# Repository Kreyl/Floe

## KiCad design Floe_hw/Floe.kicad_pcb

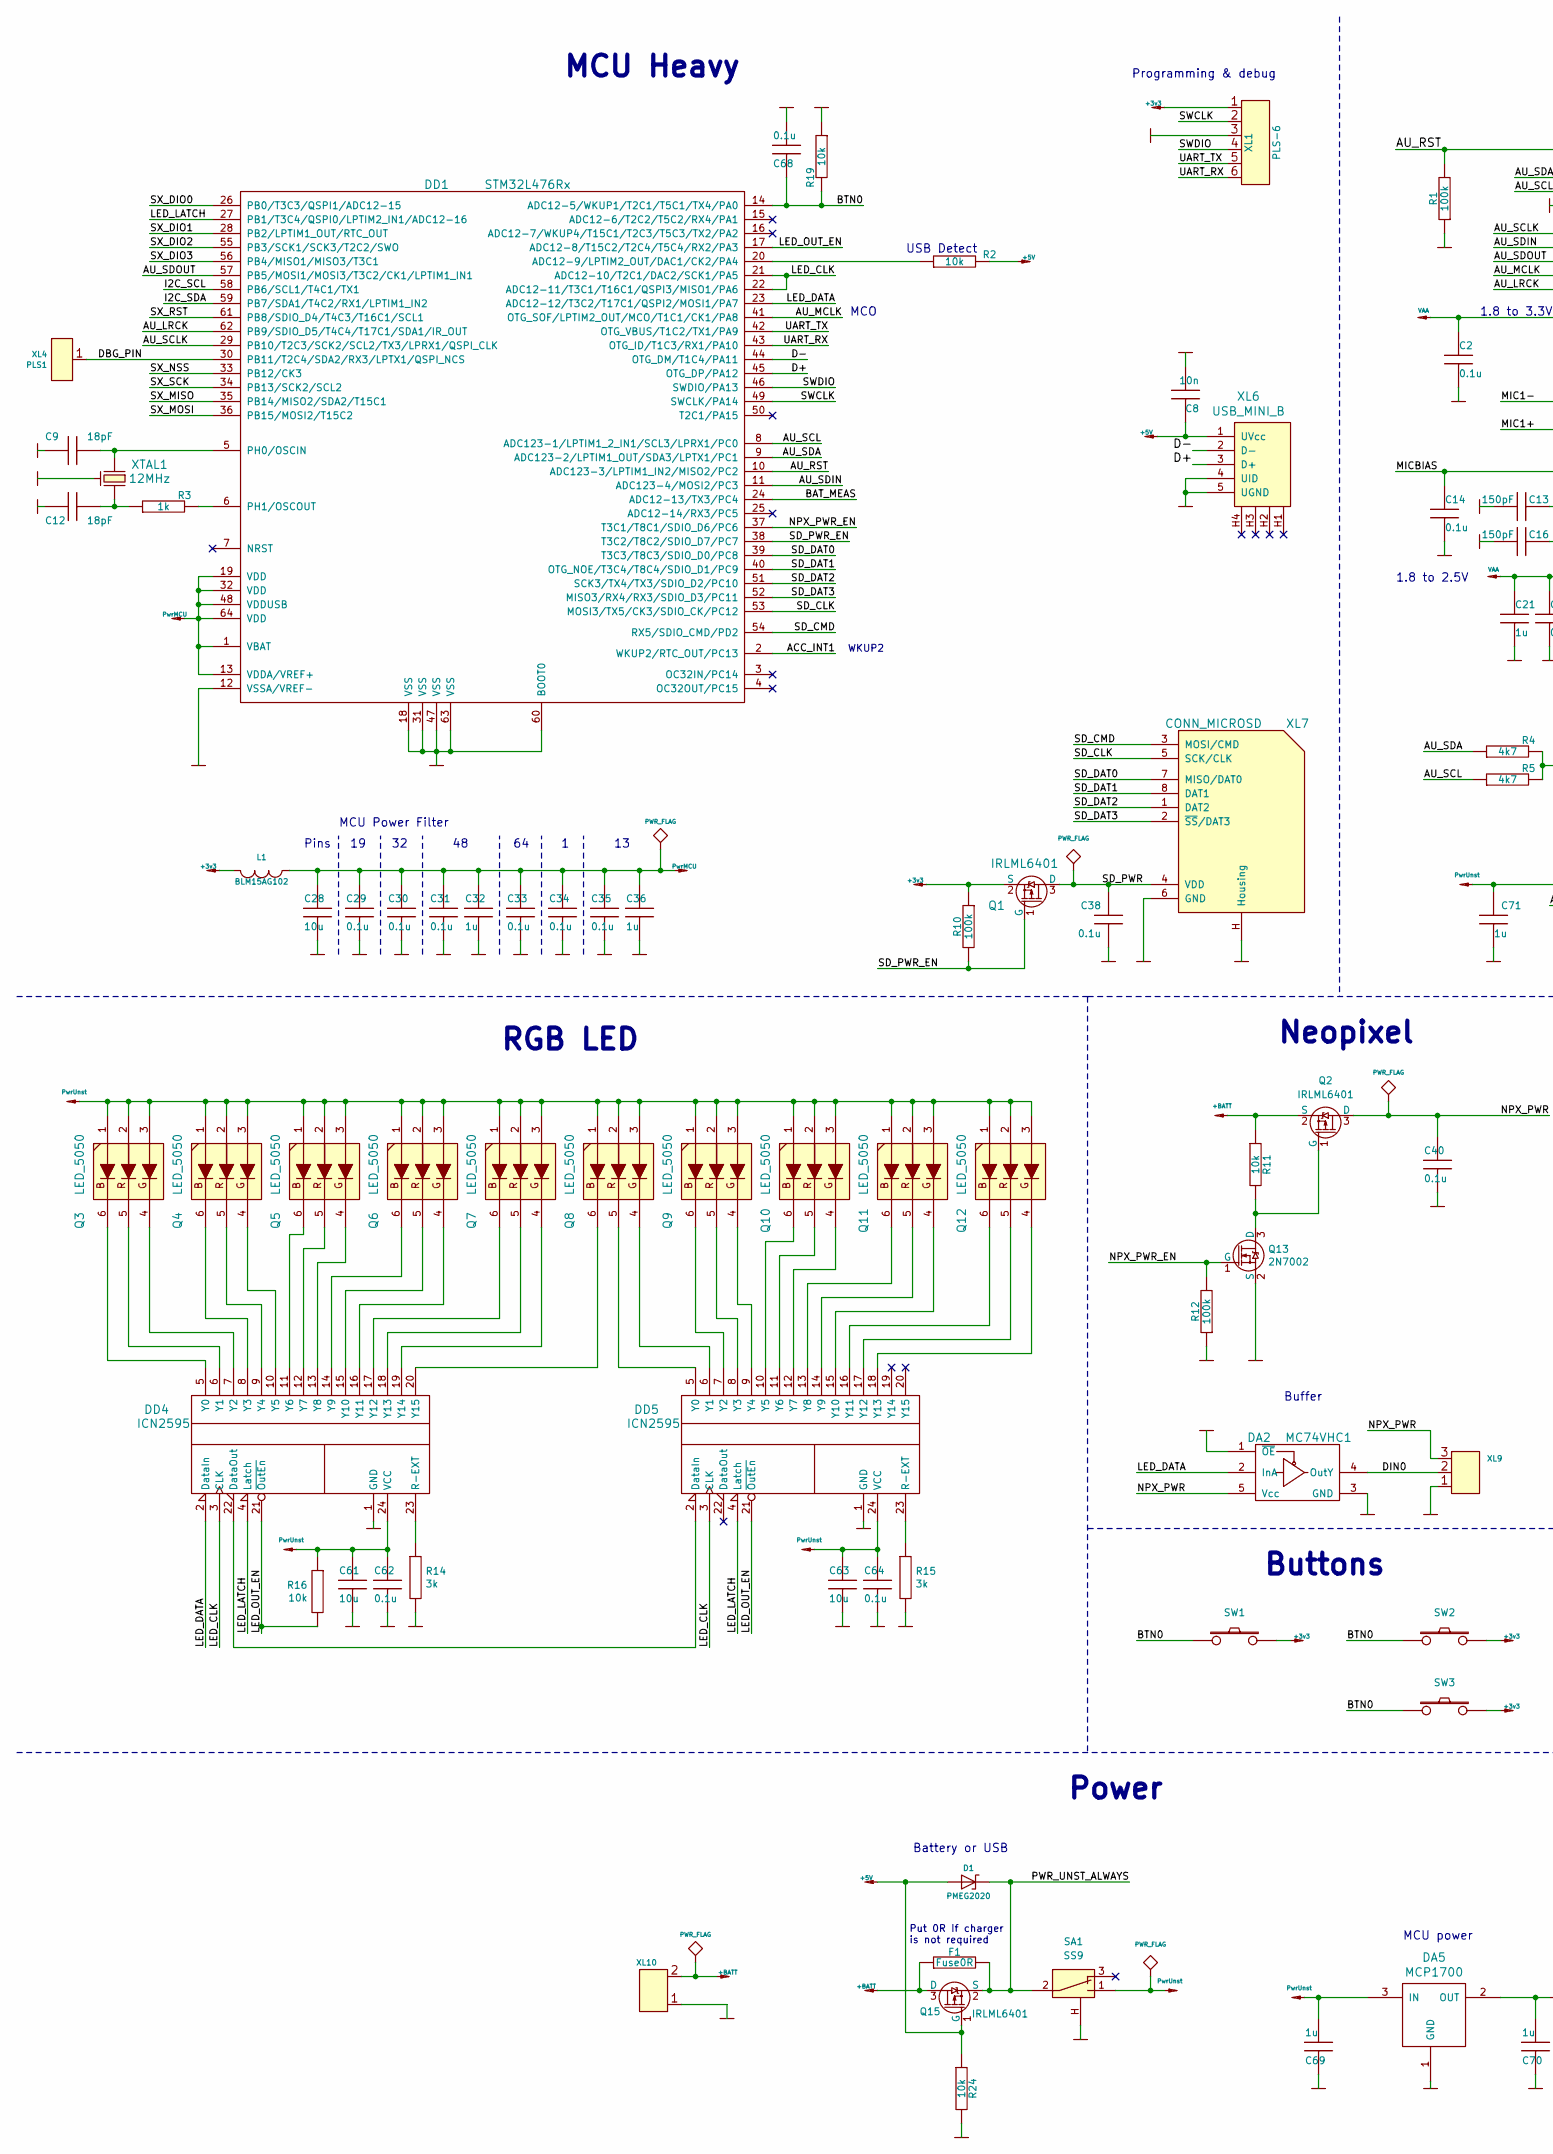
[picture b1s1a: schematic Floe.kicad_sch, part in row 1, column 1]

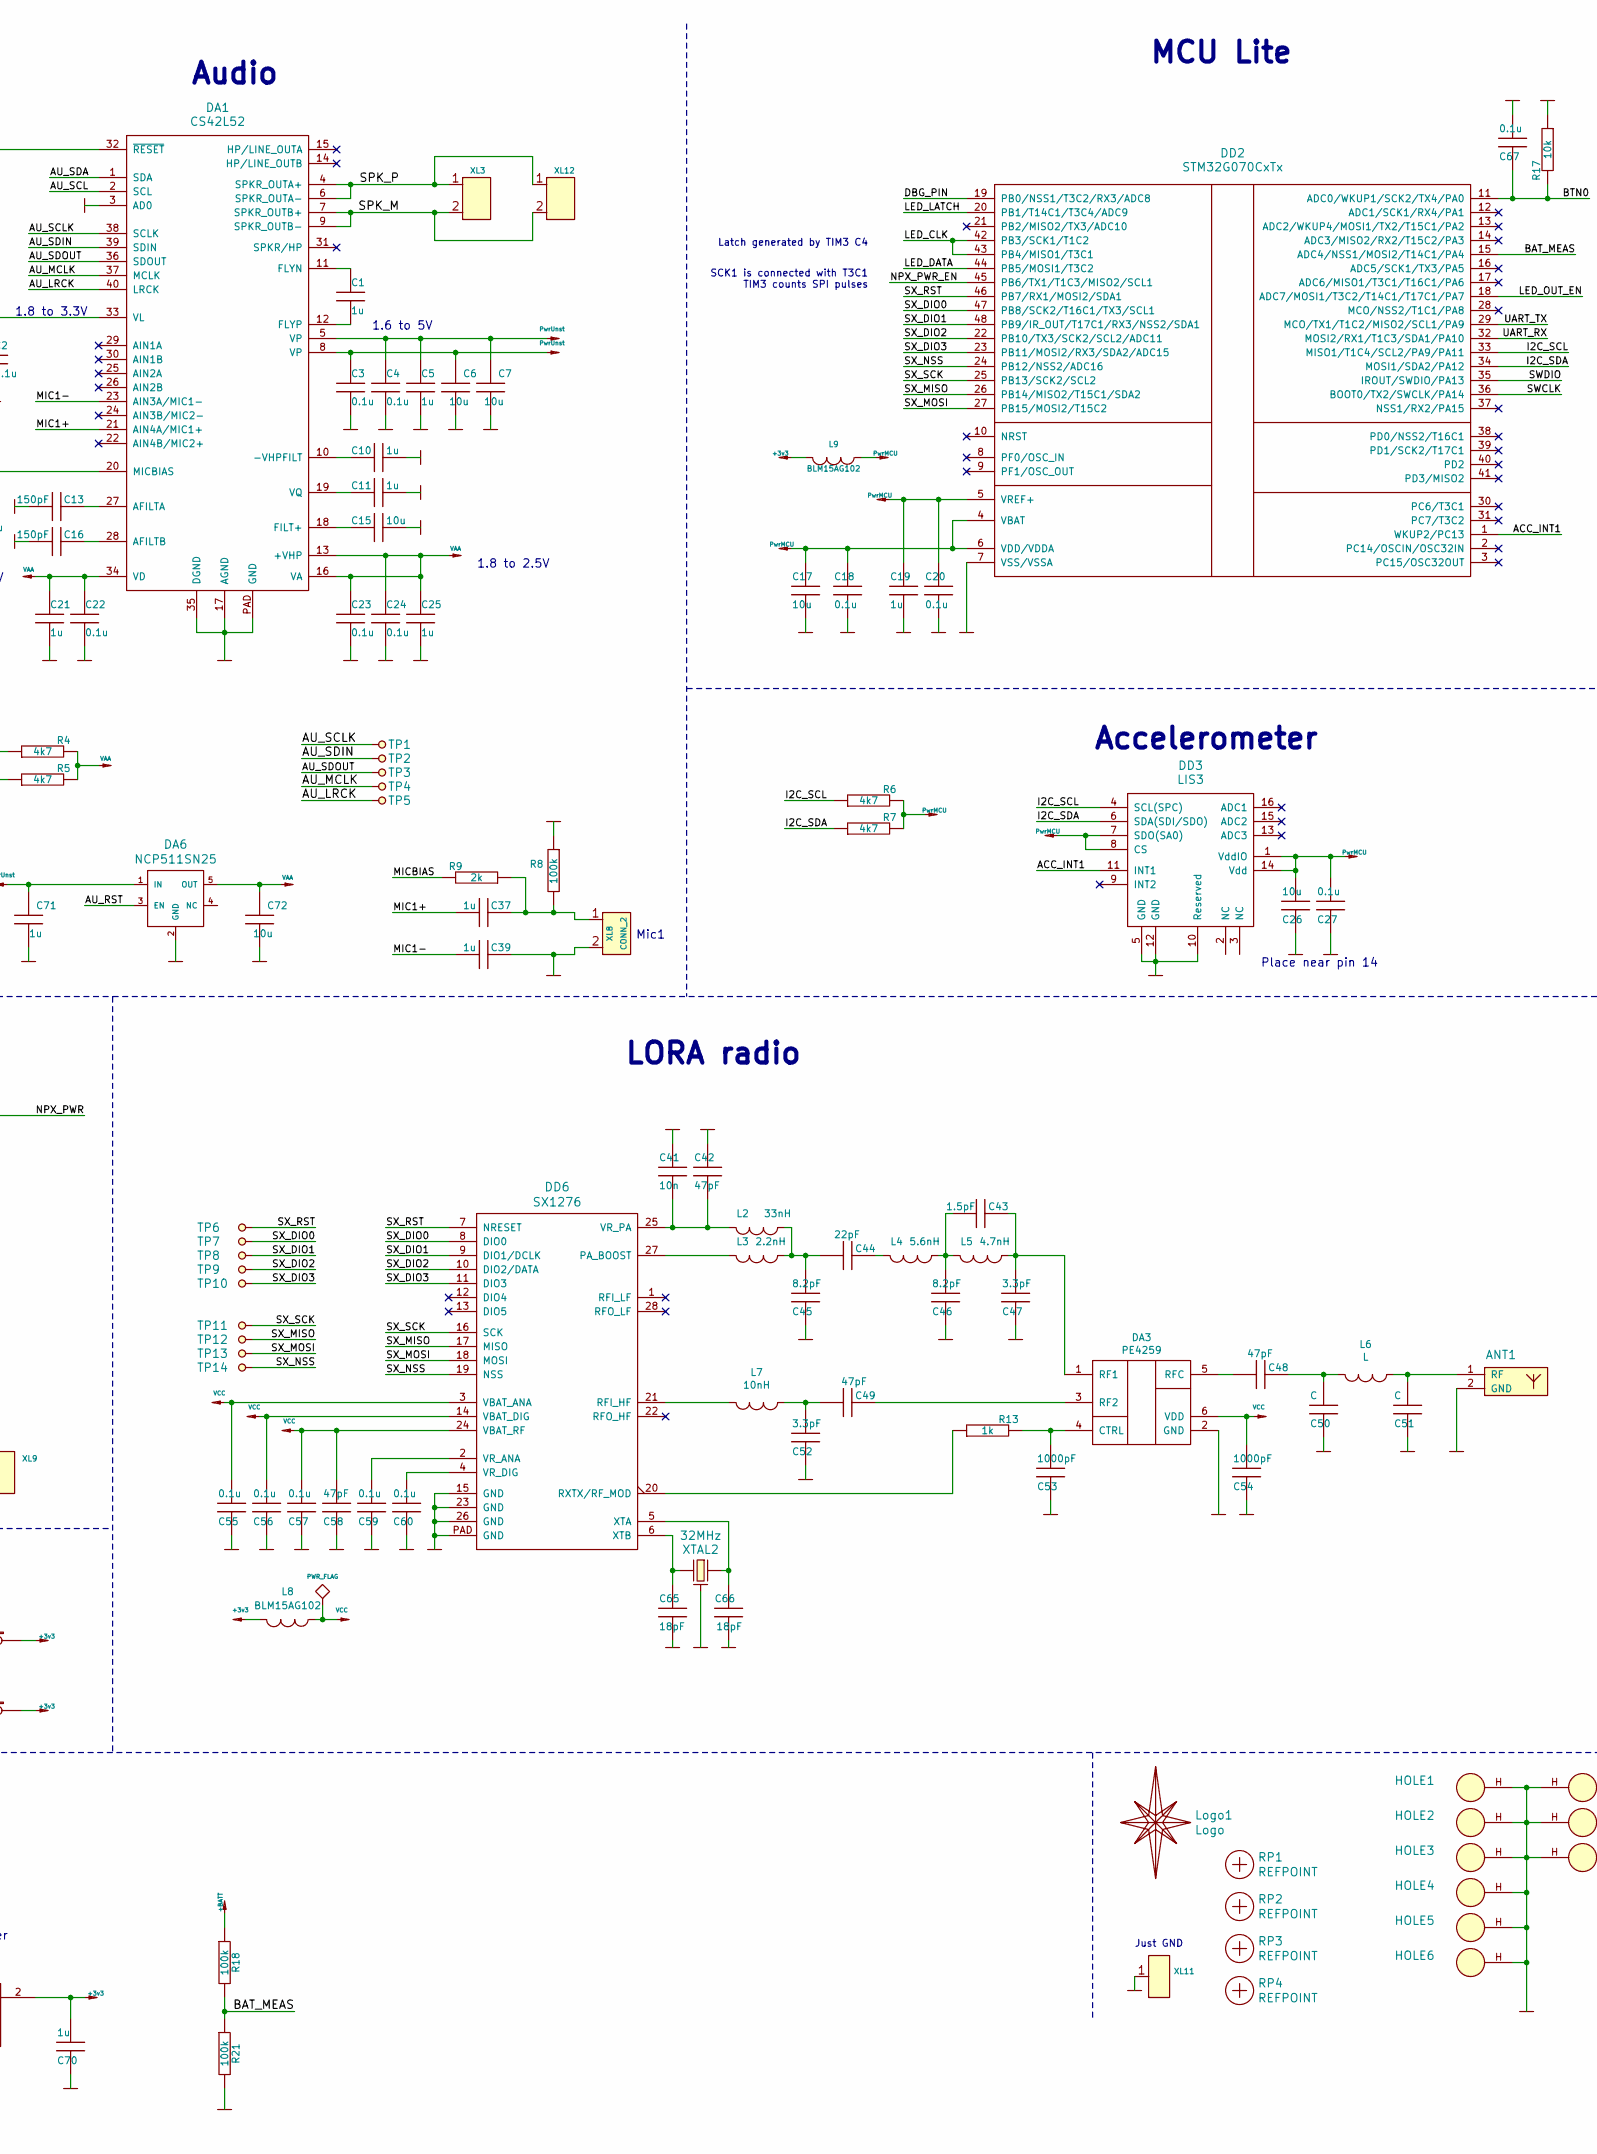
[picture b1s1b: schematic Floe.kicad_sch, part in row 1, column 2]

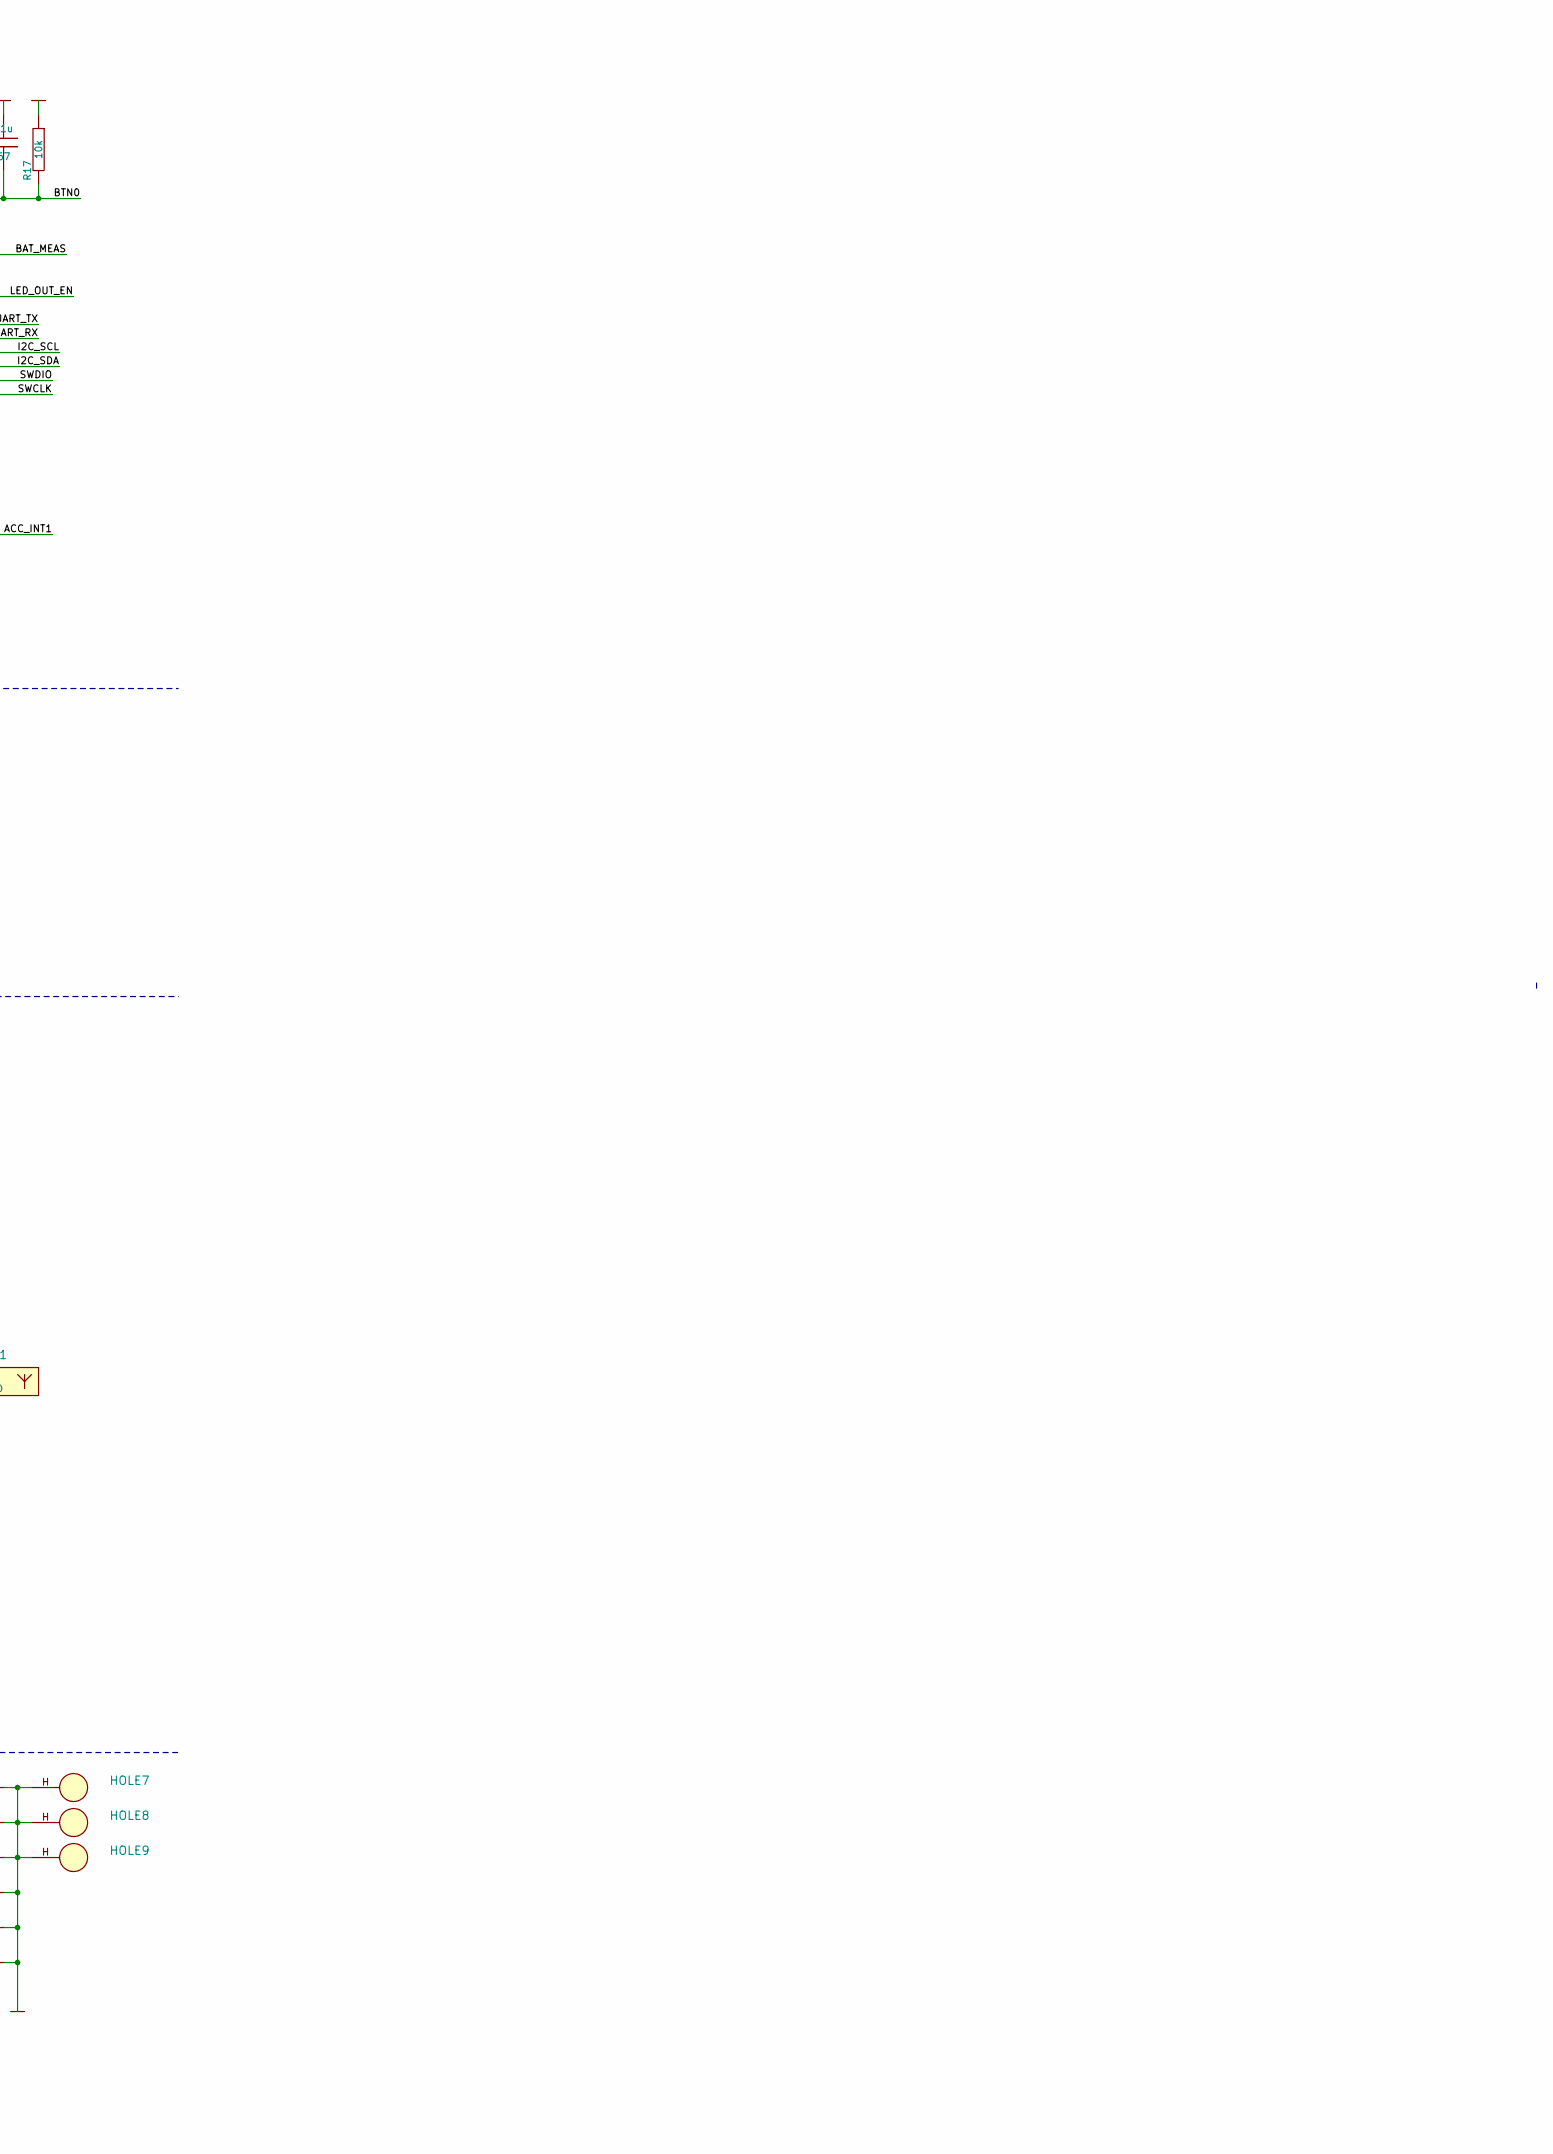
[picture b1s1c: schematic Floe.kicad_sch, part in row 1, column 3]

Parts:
ANT1: ANT_GENERAL; ANT_IFA_MUSHROOM
C1, C5, C10, C11, C19, C21, C25, C32, C36, C37, C39, C69, C70, C71: 1u; CAP_0603_Silks
C2, C3, C4, C14, C18, C20, C22, C23, C24, C27, C29, C30, C31, C33, C34, C35, C38, C40, C62, C64, C67, C68: 0.1u; CAP_0603_Silks
C6, C7, C15, C17, C26, C28, C61, C63, C72: 10u; CAP_0603_Silks
C8: 10n; CAP_0603_Silks
C9, C12, C65, C66: 18pF; CAP_0603_Silks
C13, C16: 150pF; CAP_0603_Silks
C41: 10n; CAP_0402
C42, C48, C49, C58: 47pF; CAP_0402
C43: 1.5pF; CAP_0402
C44: 22pF; CAP_0402
C45, C46: 8.2pF; CAP_0402
C47, C52: 3.3pF; CAP_0402
C50, C51: C; CAP_0402
C53, C54: 1000pF; CAP_0402
C55, C56, C57, C59, C60: 0.1u; CAP_0402
D1: PMEG2020; SOD323
DA1: CS42L52; QFN40
DA2: MC74VHC1; SOT23-5
DA3: PE4259; SC70
DA5: MCP1700; SOT23-3A
DA6: NCP511SN25; SOT23-5
DD1: STM32L476Rx; LQFP64
DD2: STM32G070CxTx; LQFP48
DD3: LIS3; LGA16_3X3_5_3
DD4, DD5: ICN2595; TSSOP24_150_0635
DD6: SX1276; QFN-28_EP_6x6_Pitch0.65mm
F1: Fuse0R; RES_0603_FUSE
HOLE1, HOLE2, HOLE3, HOLE4, HOLE5, HOLE6: HOLE_METALLED; Hole3d5_out10mm
HOLE7, HOLE8, HOLE9: HOLE_METALLED; Hole3d3_out5d5mm
L1, L8, L9: BLM15AG102; IND_0402
L2: 33nH; IND_0402
L3: 2.2nH; IND_0402
L4: 5.6nH; IND_0402
L5: 4.7nH; IND_0402
L6: L; IND_0402
L7: 10nH; IND_0402
Logo1: Logo; Ostranna_16d9_13d5
Q1, Q2, Q15: IRLML6401; SOT23-3
Q3, Q4, Q5, Q6, Q7, Q8, Q9, Q10, Q11, Q12: LED_5050
Q13: 2N7002; SOT23-3
R1, R8, R10, R12, R18, R21: 100k; RES_0603
R2, R11, R16, R17, R19, R24: 10k; RES_0603
R3, R13: 1k; RES_0603
R4, R5, R6, R7: 4k7; RES_0603
R9: 2k; RES_0603
R14, R15: 3k; RES_0603
RP1, RP2, RP3, RP4: REFPOINT; REF_POINT_2MM
SA1: SS9; SW_SS9
SW1, SW2, SW3: BUTTON; BTN_4x4_SMD
TP1, TP2, TP3, TP4, TP5, TP6, TP7, TP8, TP9, TP10, TP11, TP12, TP13, TP14: TESTPOINT; TESTPOINT_1MM
XL1: PLS-6; PLS-6_LOCK
XL3: CONN_2; WB-02(MW-2M)
XL4: PLS1; PLS-1Rnd
XL6: USB_MINI_B; USBmicro_MOLEX_1050170001
XL7: CONN_MICROSD; MICROSD_CAP_FIX05A
XL8: CONN_2; WB-02(MW-2M)LongContacts
XL9: CONN_3; SLD_3_2D5
XL10, XL12: CONN_2; SLD_2_2D5_1mm
XL11: CONN_1; PLS-1Rnd
XTAL1: 12MHz; 03225C4
XTAL2: 32MHz; 03225C4

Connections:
+3v3: C70.1, DA5.2 (OUT), L1.2, L8.2, L9.2, Q1.2 (S), R10.1, SW1.2, SW2.2, SW3.2, XL1.1
+5v: C8.2, D1.A, Q15.1 (G), R2.2, R24.1, XL6.1 (UVcc)
+BATT: F1.1, Q2.2 (S), Q15.3 (D), R11.1, R18.1, XL10.2 (PM)
/ACC_INT1: DD1.2 (WKUP2/RTC_OUT/PC13), DD2.1 (WKUP2/PC13), DD3.11 (INT1)
/AU_LRCK: DA1.40 (LRCK), DD1.62 (PB9/SDIO_D5/T4C4/T17C1/SDA1/IR_OUT), TP5.1
/AU_MCLK: DA1.37 (MCLK), DD1.41 (OTG_SOF/LPTIM2_OUT/MCO/T1C1/CK1/PA8), TP4.1
/AU_RST: DA1.32 (~RESET), DA6.3 (EN), DD1.10 (ADC123-3/LPTIM1_IN2/MISO2/PC2), R1.2
/AU_SCL: DA1.2 (SCL), DD1.8 (ADC123-1/LPTIM1_2_IN1/SCL3/LPRX1/PC0), R5.1
/AU_SCLK: DA1.38 (SCLK), DD1.29 (PB10/T2C3/SCK2/SCL2/TX3/LPRX1/QSPI_CLK), TP1.1
/AU_SDA: DA1.1 (SDA), DD1.9 (ADC123-2/LPTIM1_OUT/SDA3/LPTX1/PC1), R4.1
/AU_SDIN: DA1.39 (SDIN), DD1.11 (ADC123-4/MOSI2/PC3), TP2.1
/AU_SDOUT: DA1.36 (SDOUT), DD1.57 (PB5/MOSI1/MOSI3/T3C2/CK1/LPTIM1_IN1), TP3.1
/BAT_MEAS: DD1.24 (ADC12-13/TX3/PC4), DD2.15 (ADC4/NSS1/MOSI2/T14C1/PA4), R18.2, R21.1
/BTN0: C67.2, C68.2, DD1.14 (ADC12-5/WKUP1/T2C1/T5C1/TX4/PA0), DD2.11 (ADC0/WKUP1/SCK2/TX4/PA0), R17.2, R19.2, SW1.1, SW2.1, SW3.1
/D+: DD1.45 (OTG_DP/PA12), XL6.3 (D+)
/D-: DD1.44 (OTG_DM/T1C4/PA11), XL6.2 (D-)
/DBG_PIN: DD1.30 (PB11/T2C4/SDA2/RX3/LPTX1/QSPI_NCS), DD2.19 (PB0/NSS1/T3C2/RX3/ADC8), XL4.1
/DIN0: DA2.4 (OutY), XL9.2 (PM)
/I2C_SCL: DD1.58 (PB6/SCL1/T4C1/TX1), DD2.33 (MISO1/T1C4/SCL2/PA9/PA11), DD3.4 (SCL(SPC)), R6.1
/I2C_SDA: DD1.59 (PB7/SDA1/T4C2/RX1/LPTIM1_IN2), DD2.34 (MOSI1/SDA2/PA12), DD3.6 (SDA(SDI/SDO)), R7.1
/LED_CLK: DD1.21 (ADC12-10/T2C1/DAC2/SCK1/PA5), DD1.22 (ADC12-11/T3C1/T16C1/QSPI3/MISO1/PA6), DD2.42 (PB3/SCK1/T1C2), DD2.43 (PB4/MISO1/T3C1), DD4.3 (CLK), DD5.3 (CLK)
/LED_DATA: DA2.2 (InA), DD1.23 (ADC12-12/T3C2/T17C1/QSPI2/MOSI1/PA7), DD2.44 (PB5/MOSI1/T3C2), DD4.2 (DataIn)
/LED_LATCH: DD1.27 (PB1/T3C4/QSPI0/LPTIM2_IN1/ADC12-16), DD2.20 (PB1/T14C1/T3C4/ADC9), DD4.4 (Latch), DD5.4 (Latch)
/LED_OUT_EN: DD1.17 (ADC12-8/T15C2/T2C4/T5C4/RX2/PA3), DD2.18 (ADC7/MOSI1/T3C2/T14C1/T17C1/PA7), DD4.21 (~OutEn), DD5.21 (~OutEn), R16.2
/MIC1+: C37.1, DA1.21 (AIN4A/MIC1+)
/MIC1-: C39.1, DA1.23 (AIN3A/MIC1-)
/MICBIAS: C14.1, DA1.20 (MICBIAS), R9.2
/NPX_PWR: C40.2, DA2.5 (Vcc), Q2.3 (D), XL9.3
/NPX_PWR_EN: DD1.37 (T3C1/T8C1/SDIO_D6/PC6), DD2.45 (PB6/TX1/T1C3/MISO2/SCL1), Q13.1 (G), R12.2
/PWR_UNST_ALWAYS: D1.C, F1.2, Q15.2 (S), SA1.2
/SD_CLK: DD1.53 (MOSI3/TX5/CK3/SDIO_CK/PC12), XL7.5 (SCK/CLK)
/SD_CMD: DD1.54 (RX5/SDIO_CMD/PD2), XL7.3 (MOSI/CMD)
/SD_DAT0: DD1.39 (T3C3/T8C3/SDIO_D0/PC8), XL7.7 (MISO/DAT0)
/SD_DAT1: DD1.40 (OTG_NOE/T3C4/T8C4/SDIO_D1/PC9), XL7.8 (DAT1)
/SD_DAT2: DD1.51 (SCK3/TX4/TX3/SDIO_D2/PC10), XL7.1 (DAT2)
/SD_DAT3: DD1.52 (MISO3/RX4/RX3/SDIO_D3/PC11), XL7.2 (~SS~/DAT3)
/SD_PWR: C38.1, Q1.3 (D), XL7.4 (VDD)
/SD_PWR_EN: DD1.38 (T3C2/T8C2/SDIO_D7/PC7), Q1.1 (G), R10.2
/SPK_M: DA1.7 (SPKR_OUTB+), DA1.9 (SPKR_OUTB-), XL3.2 (PM), XL12.2 (PM)
/SPK_P: DA1.4 (SPKR_OUTA+), DA1.6 (SPKR_OUTA-), XL3.1, XL12.1
/SWCLK: DD1.49 (SWCLK/PA14), DD2.36 (BOOT0/TX2/SWCLK/PA14), XL1.2
/SWDIO: DD1.46 (SWDIO/PA13), DD2.35 (IROUT/SWDIO/PA13), XL1.4
/SX_DIO0: DD1.26 (PB0/T3C3/QSPI1/ADC12-15), DD2.47 (PB8/SCK2/T16C1/TX3/SCL1), DD6.8 (DIO0), TP7.1
/SX_DIO1: DD1.28 (PB2/LPTIM1_OUT/RTC_OUT), DD2.48 (PB9/IR_OUT/T17C1/RX3/NSS2/SDA1), DD6.9 (DIO1/DCLK), TP8.1
/SX_DIO2: DD1.55 (PB3/SCK1/SCK3/T2C2/SWO), DD2.22 (PB10/TX3/SCK2/SCL2/ADC11), DD6.10 (DIO2/DATA), TP9.1
/SX_DIO3: DD1.56 (PB4/MISO1/MISO3/T3C1), DD2.23 (PB11/MOSI2/RX3/SDA2/ADC15), DD6.11 (DIO3), TP10.1
/SX_MISO: DD1.35 (PB14/MISO2/SDA2/T15C1), DD2.26 (PB14/MISO2/T15C1/SDA2), DD6.17 (MISO), TP12.1
/SX_MOSI: DD1.36 (PB15/MOSI2/T15C2), DD2.27 (PB15/MOSI2/T15C2), DD6.18 (MOSI), TP13.1
/SX_NSS: DD1.33 (PB12/CK3), DD2.24 (PB12/NSS2/ADC16), DD6.19 (NSS), TP14.1
/SX_RST: DD1.61 (PB8/SDIO_D4/T4C3/T16C1/SCL1), DD2.46 (PB7/RX1/MOSI2/SDA1), DD6.7 (NRESET), TP6.1
/SX_SCK: DD1.34 (PB13/SCK2/SCL2), DD2.25 (PB13/SCK2/SCL2), DD6.16 (SCK), TP11.1
/UART_RX: DD1.43 (OTG_ID/T1C3/RX1/PA10), DD2.32 (MOSI2/RX1/T1C3/SDA1/PA10), XL1.6
/UART_TX: DD1.42 (OTG_VBUS/T1C2/TX1/PA9), DD2.29 (MCO/TX1/T1C2/MISO2/SCL1/PA9), XL1.5
GND: ANT1.2 (GND), C2.2, C3.2, C4.2, C5.2, C6.2, C7.2, C8.1, C9.2, C10.1, C11.1, C12.2, C13.1, C14.2, C15.1, C16.1, C17.1, C18.1, C19.1, C20.1, C21.2, C22.2, C23.2, C24.2, C25.2, C26.2, C27.2, C28.1, C29.1, C30.1, C31.1, C32.1, C33.1, C34.1, C35.1, C36.1, C38.2, C39.2, C40.1, C41.2, C42.2, C45.2, C46.2, C47.2, C50.2, C51.2, C52.2, C53.2, C54.2, C55.2, C56.2, C57.2, C58.2, C59.2, C60.2, C61.1, C62.1, C63.1, C64.1, C65.2, C66.2, C67.1, C68.1, C69.2, C70.2, C71.2, C72.2, DA1.3 (AD0), DA1.17 (AGND), DA1.35 (DGND), DA1.PAD (GND), DA2.1 (~OE), DA2.3 (GND), DA3.2 (GND), DA5.1 (GND), DA6.2 (GND), DD1.12 (VSSA/VREF-), DD1.18 (VSS), DD1.31 (VSS), DD1.47 (VSS)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
unnamed: ANT1.1 (RF), C51.1, L6.2
unnamed: C1.1, DA1.11 (FLYN)
unnamed: C1.2, DA1.12 (FLYP)
unnamed: C9.1, DD1.5 (PH0/OSCIN), XTAL1.1
unnamed: C10.2, DA1.10 (-VHPFILT)
unnamed: C11.2, DA1.19 (VQ)
unnamed: C12.1, R3.1, XTAL1.2
unnamed: C13.2, DA1.27 (AFILTA)
unnamed: C15.2, DA1.18 (FILT+)
unnamed: C16.2, DA1.28 (AFILTB)
unnamed: C37.2, R8.2, R9.1, XL8.1
unnamed: C41.1, C42.1, DD6.25 (VR_PA), L2.1
unnamed: C43.1, C47.1, DA3.1 (RF1), L5.2
unnamed: C43.2, C46.1, L4.2, L5.1
unnamed: C44.1, L4.1
unnamed: C44.2, C45.1, L2.2, L3.2
unnamed: C48.1, C50.1, L6.1
unnamed: C48.2, DA3.5 (RFC)
unnamed: C49.1, DA3.3 (RF2)
unnamed: C49.2, C52.1, L7.2
unnamed: C53.1, DA3.4 (CTRL), R13.2
unnamed: C59.1, DD6.2 (VR_ANA)
unnamed: C60.1, DD6.4 (VR_DIG)
unnamed: C65.1, DD6.6 (XTB), XTAL2.2
unnamed: C66.1, DD6.5 (XTA), XTAL2.1
unnamed: DD1.6 (PH1/OSCOUT), R3.2
unnamed: DD1.20 (ADC12-9/LPTIM2_OUT/DAC1/CK2/PA4), R2.1
unnamed: DD4.5 (Y0), Q3.6
unnamed: DD4.6 (Y1), Q3.5 (G)
unnamed: DD4.7 (Y2), Q3.4 (B)
unnamed: DD4.8 (Y3), Q4.6
unnamed: DD4.9 (Y4), Q4.5 (G)
unnamed: DD4.10 (Y5), Q4.4 (B)
unnamed: DD4.11 (Y6), Q5.6
unnamed: DD4.12 (Y7), Q5.5 (G)
unnamed: DD4.13 (Y8), Q5.4 (B)
unnamed: DD4.14 (Y9), Q6.6
unnamed: DD4.15 (Y10), Q6.5 (G)
unnamed: DD4.16 (Y11), Q6.4 (B)
unnamed: DD4.17 (Y12), Q7.6
unnamed: DD4.18 (Y13), Q7.5 (G)
unnamed: DD4.19 (Y14), Q7.4 (B)
unnamed: DD4.20 (Y15), Q8.6
unnamed: DD4.22 (DataOut), DD5.2 (DataIn)
unnamed: DD4.23 (R-EXT), R14.1
unnamed: DD5.5 (Y0), Q8.5 (G)
unnamed: DD5.6 (Y1), Q8.4 (B)
unnamed: DD5.7 (Y2), Q9.6
unnamed: DD5.8 (Y3), Q9.5 (G)
unnamed: DD5.9 (Y4), Q9.4 (B)
unnamed: DD5.10 (Y5), Q10.6
unnamed: DD5.11 (Y6), Q10.5 (G)
unnamed: DD5.12 (Y7), Q10.4 (B)
unnamed: DD5.13 (Y8), Q11.6
unnamed: DD5.14 (Y9), Q11.5 (G)
unnamed: DD5.15 (Y10), Q11.4 (B)
unnamed: DD5.16 (Y11), Q12.6
unnamed: DD5.17 (Y12), Q12.5 (G)
unnamed: DD5.18 (Y13), Q12.4 (B)
unnamed: DD5.23 (R-EXT), R15.1
unnamed: DD6.20 (RXTX/RF_MOD), R13.1
unnamed: DD6.21 (RFI_HF), L7.1
unnamed: DD6.27 (PA_BOOST), L3.1
unnamed: Q2.1 (G), Q13.3 (D), R11.2
PwrMCU: C17.2, C18.2, C19.2, C20.2, C26.1, C27.1, C28.2, C29.2, C30.2, C31.2, C32.2, C33.2, C34.2, C35.2, C36.2, DD1.1 (VBAT), DD1.13 (VDDA/VREF+), DD1.19 (VDD), DD1.32 (VDD), DD1.48 (VDDUSB), DD1.64 (VDD), DD2.4 (VBAT), DD2.5 (VREF+), DD2.6 (VDD/VDDA), DD3.1 (VddIO), DD3.7 (SDO(SA0)), DD3.8 (CS), DD3.14 (Vdd), L1.1, L9.1, R6.2, R7.2
PwrUnst: C3.1, C4.1, C5.1, C6.1, C7.1, C61.2, C62.2, C63.2, C64.2, C69.1, C71.1, DA1.5 (VP), DA1.8 (VP), DA5.3 (IN), DA6.1 (IN), DD4.24 (VCC), DD5.24 (VCC), Q3.1, Q3.2, Q3.3, Q4.1, Q4.2, Q4.3, Q5.1, Q5.2, Q5.3, Q6.1, Q6.2, Q6.3, Q7.1, Q7.2, Q7.3, Q8.1, Q8.2, Q8.3, Q9.1, Q9.2, Q9.3, Q10.1, Q10.2, Q10.3, Q11.1, Q11.2, Q11.3, Q12.1, Q12.2, Q12.3, R16.1, SA1.1
VAA: C2.1, C21.1, C22.1, C23.1, C24.1, C25.1, C72.1, DA1.13 (+VHP), DA1.16 (VA), DA1.33 (VL), DA1.34 (VD), DA6.5 (OUT), R4.2, R5.2
VCC: C54.1, C55.1, C56.1, C57.1, C58.1, DA3.6 (VDD), DD6.3 (VBAT_ANA), DD6.14 (VBAT_DIG), DD6.24 (VBAT_RF), L8.1

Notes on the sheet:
Pins 19 32 48 64 1 13
MCU Power Filter
RGB LED
MCU Heavy
MCO
WKUP2
USB Detect
Put 0R If charger is not required
Battery or USB
Power
Buttons
Programming & debug
Neopixel
Buffer
1.8 to 2.5V
MCU power
1.8 to 3.3V
Audio
1.6 to 5V
LORA radio
Mic1
Latch generated by TIM3 C4
SCK1 is connected with T3C1 TIM3 counts SPI pulses
Accelerometer
MCU Lite
Just GND
Place near pin 14

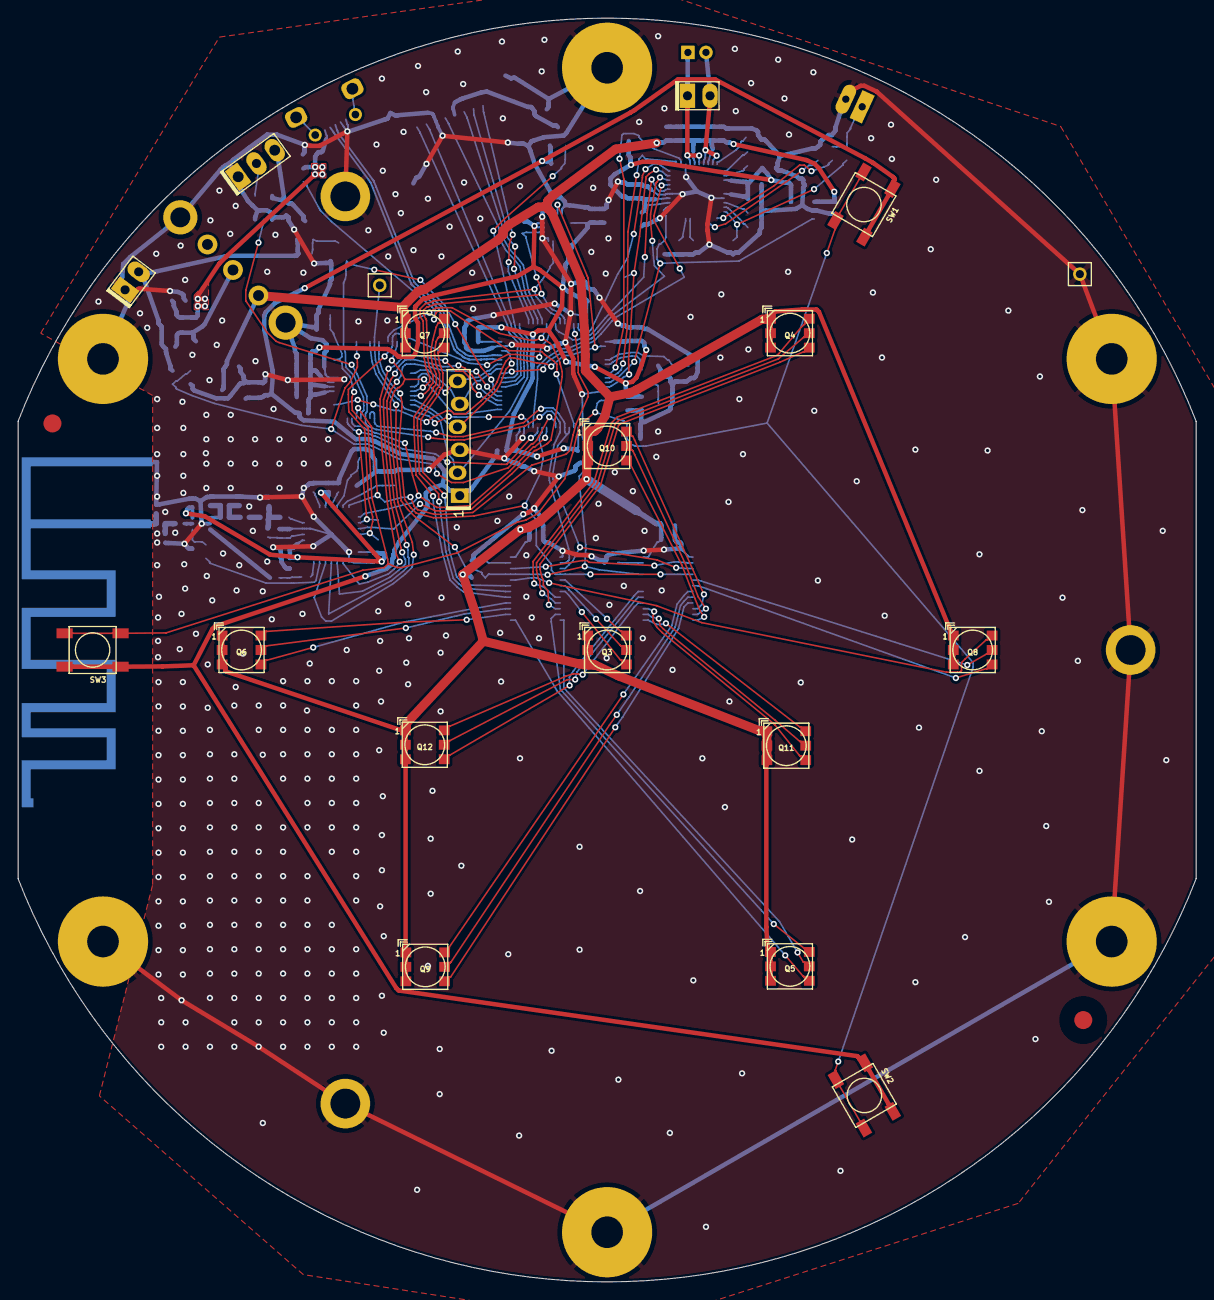
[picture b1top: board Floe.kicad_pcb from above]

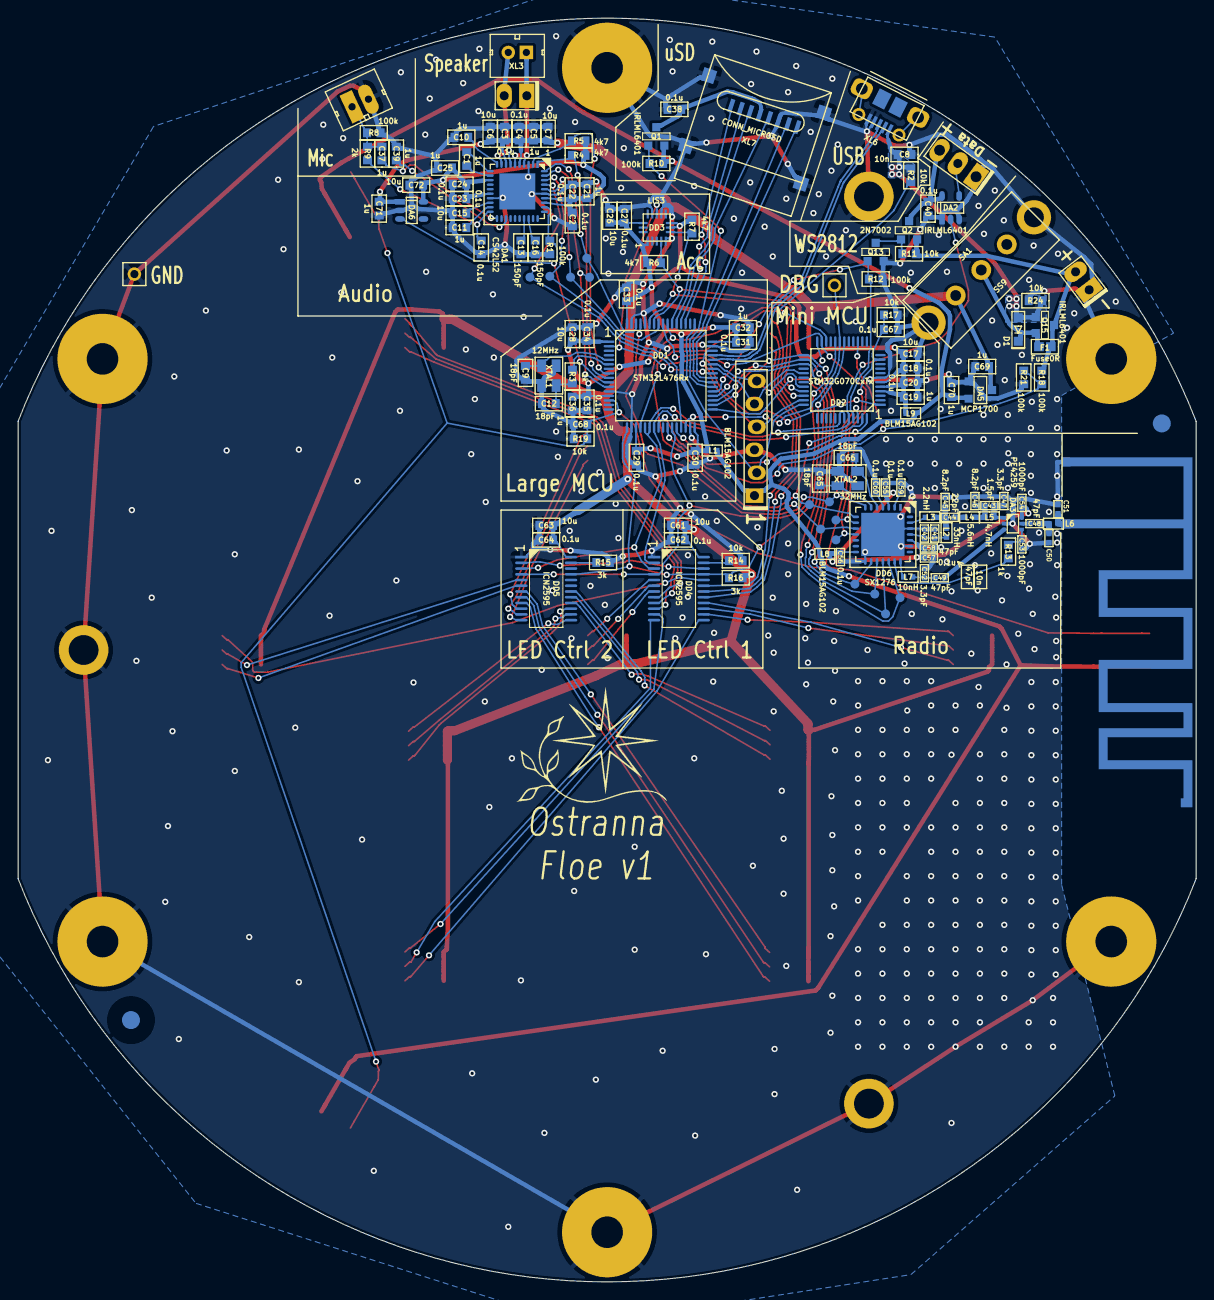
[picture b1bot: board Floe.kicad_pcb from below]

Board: 2 copper layers, 130.5 x 140.0 mm, 174 parts (147 on the bottom side), 122 nets.

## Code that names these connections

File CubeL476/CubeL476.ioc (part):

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Mcu.Name=STM32L476R(C-E-G)Tx
Mcu.Package=LQFP64
Mcu.UserName=STM32L476RCTx
PA0.Mode=SYS_WakeUp0
PA0.Signal=SYS_WKUP1
PA10.Mode=Asynchronous
PA10.Signal=USART1_RX
PA11.Mode=Device_Only
PA11.Signal=USB_OTG_FS_DM
PA12.Mode=Device_Only
PA12.Signal=USB_OTG_FS_DP
PA13\ (JTMS-SWDIO).Mode=Serial_Wire
PA13\ (JTMS-SWDIO).Signal=SYS_JTMS-SWDIO
PA14\ (JTCK-SWCLK).Mode=Serial_Wire
PA14\ (JTCK-SWCLK).Signal=SYS_JTCK-SWCLK
PA3.Signal=S_TIM15_CH2
PA5.Mode=TX_Only_Simplex_Unidirect_Master
PA5.Signal=SPI1_SCK
PA6.Signal=S_TIM3_CH1
PA7.Mode=TX_Only_Simplex_Unidirect_Master
PA7.Signal=SPI1_MOSI
PA8.Mode=Clock-out
PA8.Signal=RCC_MCO
PA9.Mode=Asynchronous
PA9.Signal=USART1_TX
PB1.Signal=S_TIM3_CH4
PB10.Mode=SAI_A_AsyncSlave
PB10.Signal=SAI1_SCK_A
PB13.Mode=Full_Duplex_Master
PB13.Signal=SPI2_SCK
PB14.Mode=Full_Duplex_Master
PB14.Signal=SPI2_MISO
PB15.Mode=Full_Duplex_Master
PB15.Signal=SPI2_MOSI
PB5.Mode=SAI_B_SyncSlave
PB5.Signal=SAI1_SD_B
PB6.Mode=I2C
PB6.Signal=I2C1_SCL
PB7.Mode=I2C
PB7.Signal=I2C1_SDA
PB9.Mode=SAI_A_AsyncSlave
PB9.Signal=SAI1_FS_A
PC0.Mode=I2C
PC0.Signal=I2C3_SCL
PC1.Mode=I2C
PC1.Signal=I2C3_SDA
PC10.Mode=SD_4_bits_Wide_bus
PC10.Signal=SDMMC1_D2
PC11.Mode=SD_4_bits_Wide_bus
PC11.Signal=SDMMC1_D3
PC12.Mode=SD_4_bits_Wide_bus
PC12.Signal=SDMMC1_CK
PC13.Mode=SYS_WakeUp1
PC13.Signal=SYS_WKUP2
PC14-OSC32_IN\ (PC14).Signal=GPIO_Input
PC15-OSC32_OUT\ (PC15).Signal=GPIO_Output
PC3.Mode=SAI_A_AsyncSlave
PC3.Signal=SAI1_SD_A
PC8.Mode=SD_4_bits_Wide_bus
PC8.Signal=SDMMC1_D0
PC9.Mode=SD_4_bits_Wide_bus
PC9.Signal=SDMMC1_D1
PD2.Mode=SD_4_bits_Wide_bus
PD2.Signal=SDMMC1_CMD
PH0-OSC_IN\ (PH0).Mode=HSE-External-Oscillator
PH0-OSC_IN\ (PH0).Signal=RCC_OSC_IN
PH1-OSC_OUT\ (PH1).Mode=HSE-External-Oscillator
PH1-OSC_OUT\ (PH1).Signal=RCC_OSC_OUT
RCC.HSE_VALUE=12000000
RCC.SYSCLKFreq_VALUE=80000000
RCC.SYSCLKSource=RCC_SYSCLKSOURCE_PLLCLK
board=custom

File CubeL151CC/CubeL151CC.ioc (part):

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Mcu.Name=STM32L151CCTx
Mcu.Package=LQFP48
Mcu.UserName=STM32L151CCTx
PA11.Mode=Device
PA11.Signal=USB_DM
PA12.Mode=Device
PA12.Signal=USB_DP
PA13.Mode=Serial_Wire
PA13.Signal=SYS_JTMS-SWDIO
PA14.Mode=Serial_Wire
PA14.Signal=SYS_JTCK-SWCLK
PA2.Mode=Asynchronous
PA2.Signal=USART2_TX
PA3.Mode=Asynchronous
PA3.Signal=USART2_RX
PA5.Mode=Full_Duplex_Master
PA5.Signal=SPI1_SCK
PA6.Mode=Full_Duplex_Master
PA6.Signal=SPI1_MISO
PA7.Mode=Full_Duplex_Master
PA7.Signal=SPI1_MOSI
PB12.Mode=Half_Duplex_Slave
PB12.Signal=I2S2_WS
PB13.Mode=Half_Duplex_Slave
PB13.Signal=I2S2_CK
PB15.Mode=Half_Duplex_Slave
PB15.Signal=I2S2_SD
PB3.Mode=Full_Duplex_Master
PB3.Signal=SPI3_SCK
PB4.Mode=Full_Duplex_Master
PB4.Signal=SPI3_MISO
PB5.Mode=Full_Duplex_Master
PB5.Signal=SPI3_MOSI
PB6.Mode=I2C
PB6.Signal=I2C1_SCL
PB7.Mode=I2C
PB7.Signal=I2C1_SDA
PH0-OSC_IN.Mode=HSE-External-Oscillator
PH0-OSC_IN.Signal=RCC_OSC_IN
PH1-OSC_OUT.Mode=HSE-External-Oscillator
PH1-OSC_OUT.Signal=RCC_OSC_OUT
RCC.HSE_VALUE=12000000
RCC.SYSCLKFreq_VALUE=32000000
RCC.SYSCLKSource=RCC_SYSCLKSOURCE_PLLCLK
board=custom

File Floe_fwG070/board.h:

#ifndef BOARD_H__
#define BOARD_H__

// ==== General ====
#define BOARD_NAME          "Floe v1"
#define APP_NAME            "FLoe"

#define STM32G070xx

#define LSE_FREQ_HZ     32768   // Left it here even if not used

// ST driver system settings
#define STM32_ST_IRQ_PRIORITY               2
#define STM32_ST_USE_TIMER                  15

#ifndef TRUE
#define TRUE            1
#endif

#if 1 // ==== Flash ====
#define FLASH_SZ            0x20000UL // 128k
#define FLASH_PAGE_SZ       2048UL // Constant, see ds
#define SETTINGS_SZ         FLASH_PAGE_SZ
#define BL_SZ_MAX           8192UL // Max sz of bootloader
#define APP_SZ_MAX          (FLASH_SZ - BL_SZ_MAX - SETTINGS_SZ)
#define FLASH_SETTINGS_ADDR (FLASH_BASE + FLASH_SZ - SETTINGS_SZ)
#define APP_START_ADDR      (FLASH_BASE + BL_SZ_MAX)
#endif

#if 1 // ========================== GPIO =======================================
// UART
#define UART_GPIO       GPIOA
#define UART_TX_PIN     9
#define UART_RX_PIN     10

// I2C
#define SCL2_GPIO       GPIOA
#define SCL2_PIN        11
#define SDA2_GPIO       GPIOA
#define SDA2_PIN        12
#define I2C2_AF         AF6

// Counts
#define LED_CNT         7UL // Max
#define LED_CHNL_CNT    (LED_CNT * 3UL)
#define LED_BYTE_CNT    4UL // 32 bits
#define LED_WORD_CNT    2UL // DISP_BYTE_CNT / 2
#define LED_IC_CNT      2UL

// Debug pin
#define DBG_PIN         GPIOB, 0
#define DBG_HI()        PinSetHi(DBG_PIN)
#define DBG_LO()        PinSetLo(DBG_PIN)
#define DBG_TOGGLE()    PinToggle(DBG_PIN)

// LEDs
#define TIMESLOT_TOP    255UL
//#define TIMESLOT_TOP    2UL
#define OUT_EN_PIN      GPIOA, 7, AF4
#define LATCH_TMR       TIM3
#define LATCH_TMR_IN    GPIOB, 4, omPushPull, pudPullDown, AF1
#define LATCH_PIN       GPIOB, 1, omPushPull, pudNone, AF1
#define LED_DATA        GPIOB, 5, omPushPull, pudNone, AF0
#define LED_CLK         GPIOB, 3, omPushPull, pudNone, AF0

// Acc
#define ACG_IRQ_PIN     GPIOC, 13

// Button
#define BTN_PIN         GPIOA, 0
#endif // GPIO

#if 1 // =========================== SPI =======================================
#define LEDS_SPI        SPI1
#endif

#if 1 // =========================== I2C =======================================
#define I2C1_ENABLED        FALSE
#define I2C2_ENABLED        TRUE
#define I2C_BAUDRATE_HZ     400000
#define I2C_USE_DMA         FALSE
#endif

#if 1 // =========================== ADC =======================================
#define ADC_ENABLED     TRUE
#define ADC_CHNL_CNT    2 // Tsns and VRef


#endif

#if 1 // =========================== Timers ====================================
#define LEDS_TIM        TIM3
#define LEDS_TIM_IRQ_VECTOR TIM3_IRQHandler

#define LEDS_DIM_TIM    TIM14
#define LEDS_DIM_CHNL   1

#define TIME_TIMER      TIM7
#define ADC_TIMER       TIM6

#endif


#if 1 // =========================== DMA =======================================
// ==== Uart ====
#define UART_DMA_TX_CHNL    7
#define UART_DMA_TX_REQID   51 // p223 of refman
#define UART_DMA_RX_CHNL    6
#define UART_DMA_RX_REQID   50 // p223 of refman

#define UART_DMA_TX_MODE (  DMA_PRIORITY_LOW | \
                            DMA_MSIZE_8_BIT | \
                            DMA_PSIZE_8_BIT | \
                            DMA_MEM_INC |       /* Memory pointer increase */ \
                            DMA_DIR_MEM2PER |    /* Direction is memory to peripheral */ \
                            DMA_TCIE         /* Enable Transmission Complete IRQ */)

#define UART_DMA_RX_MODE (  DMA_PRIORITY_MEDIUM | \
                            DMA_MSIZE_8_BIT | \
                            DMA_PSIZE_8_BIT | \
                            DMA_MEM_INC |       /* Memory pointer increase */ \
                            DMA_DIR_PER2MEM |    /* Direction is peripheral to memory */ \
                            DMA_CIRC         /* Circular buffer enable */)

// ==== LEDs ====
#define LEDS_DMA_TX_CHNL    1
#define LEDS_DMA_TX_REQID   17 // SPI1 TX, p223 of refman


// ==== I2C1 ====
#define I2C1_DMA_TX_CHNL    5
#define I2C1_DMA_TX_REQID   11
#define I2C1_DMA_RX_CHNL    4
#define I2C1_DMA_RX_REQID   10

// ==== ADC ====
//#define ADC_DMA_CHNL
//#define ADC_DMA_REQID       5

#endif // DMA

#if 1 // ========================== USART ======================================
#define PRINTF_FLOAT_EN     FALSE
#define UART_TXBUF_SZ       512
#define UART_RXBUF_SZ       256
#define CMD_BUF_SZ          128
#define UART_CHAR_TO_IRQ    '\n'

#define CMD_UART_PARAMS \
    USART1, UART_GPIO, UART_TX_PIN, UART_GPIO, UART_RX_PIN, \
    UART_DMA_TX_CHNL, UART_DMA_RX_CHNL, \
    UART_DMA_TX_MODE, UART_DMA_RX_MODE,\
    UART_DMA_TX_REQID, UART_DMA_RX_REQID, \
     uartclkPCLK

#endif

#endif //BOARD_H__

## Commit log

2020-10-26 + Sch started
2020-10-27 + Sch seems done
2020-11-02 + simple sch
2020-11-04 Back to huge
2020-11-05 + PCB is ready
2020-11-28 + Leds are ok
2020-11-28 + Static sequence
2020-11-28 + Effect with stages. Not good as LEDs change simultaneously.
2020-11-28 * Independent
2020-11-29 + Good Effects + i2c started
2020-12-03 + Chibios
2020-12-04 + Messages + Uart cmd works
2020-12-06 + Acc data output @100Hz + Effects work
2020-12-06 + Eff switch
2020-12-06 + FloeTypes + Button + Eff switch
2020-12-06 + Power-on Delay
2020-12-08 + First version of knock
2020-12-10 Algo2
2020-12-10 + Knock detection by measuring vector length + Lis' FIFO engaged
2020-12-13 no message
2020-12-13 + Settings save and load
2020-12-14 Types are hardcoded
2020-12-17 + Knock works ok, wave works somehow
2020-12-17 + Wave + Knock work ok
2020-12-17 Motion thread hangs with queue in effects
2021-11-04 Seems like release
2024-05-17 Moved to YaStudio IDE
